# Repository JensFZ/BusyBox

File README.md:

# BusyBox

In diesen Projekt geht es darum, dass man einen Status einer Website abfragt und, je nach rückgabe, eine grüne oder rote LED Schaltet.

der Web API Code wird demnächst auch hier noch hochgeladen

## Einrichtung Arduino IDE

- zusützliche Boardverwalter URL: http://arduino.esp8266.com/stable/package_esp8266com_index.json
- über den Boardverwalter nun das Board "esp8266" suchen und installieren
- Als Board nun über "Werkzeuge" -> "Board" -> "ESP8266 Boards" -> "NodeMCU 1.0 (ESP-12E Module)" auswählen
- Uploadspeed auf 115200 stellen
- Port auf den entsprechenden COM Port stellen

## Verwendete Hardware
- 1x NodeMCU Lua Amica Modul V2 ESP8266 ESP-12F
- 1x LED Green
- 1x LED Red
- 1x DIP-Switch 2 Slide
- 5x 1k Wiederstand
- optional LCD 16x2 i2c

## Contributing
Pull requests sind wilkommen. Bei größeren Änderungen eröffnen Sie bitte zunächst ein Issue, um zu besprechen, was Sie ändern möchten.

## License
[MIT](https://choosealicense.com/licenses/mit/)

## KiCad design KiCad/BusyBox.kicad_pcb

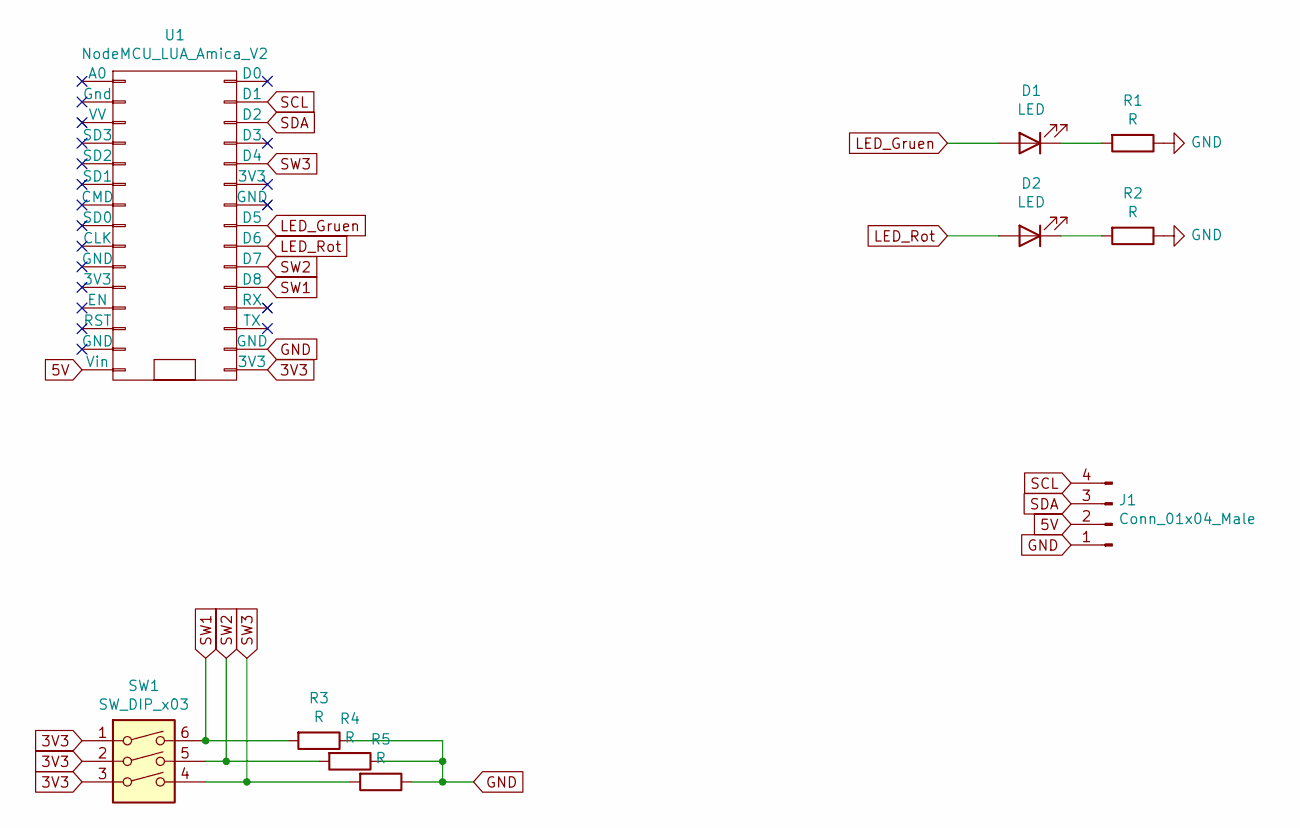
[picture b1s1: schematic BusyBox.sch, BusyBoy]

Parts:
D1, D2: LED; LED_D5.0mm
J1: Conn_01x04_Male; PinHeader_1x04_P2.54mm_Vertical
R1, R2, R3, R4, R5: R; R_Axial_DIN0207_L6.3mm_D2.5mm_P10.16mm_Horizontal
SW1: SW_DIP_x03; SW_DIP_SPSTx03_Slide_9.78x9.8mm_W7.62mm_P2.54mm
U1: NodeMCU_LUA_Amica_V2; NodeMCU-LoLinV3

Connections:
3V3: SW1.1, SW1.2, SW1.3, U1.16 (3V3)
5V: J1.2, U1.15 (Vin)
GND: J1.1, R1.1, R2.1, R3.1, R4.1, R5.1, U1.17 (GND)
LED_Gruen: D1.2 (A), U1.23 (D5)
LED_Rot: D2.2 (A), U1.22 (D6)
unnamed: D1.1 (K), R1.2
unnamed: D2.1 (K), R2.2
SCL: J1.4, U1.29 (D1)
SDA: J1.3, U1.28 (D2)
SW1: R3.2, SW1.6, U1.20 (D8)
SW2: R4.2, SW1.5, U1.21 (D7)
SW3: R5.2, SW1.4, U1.26 (D4)

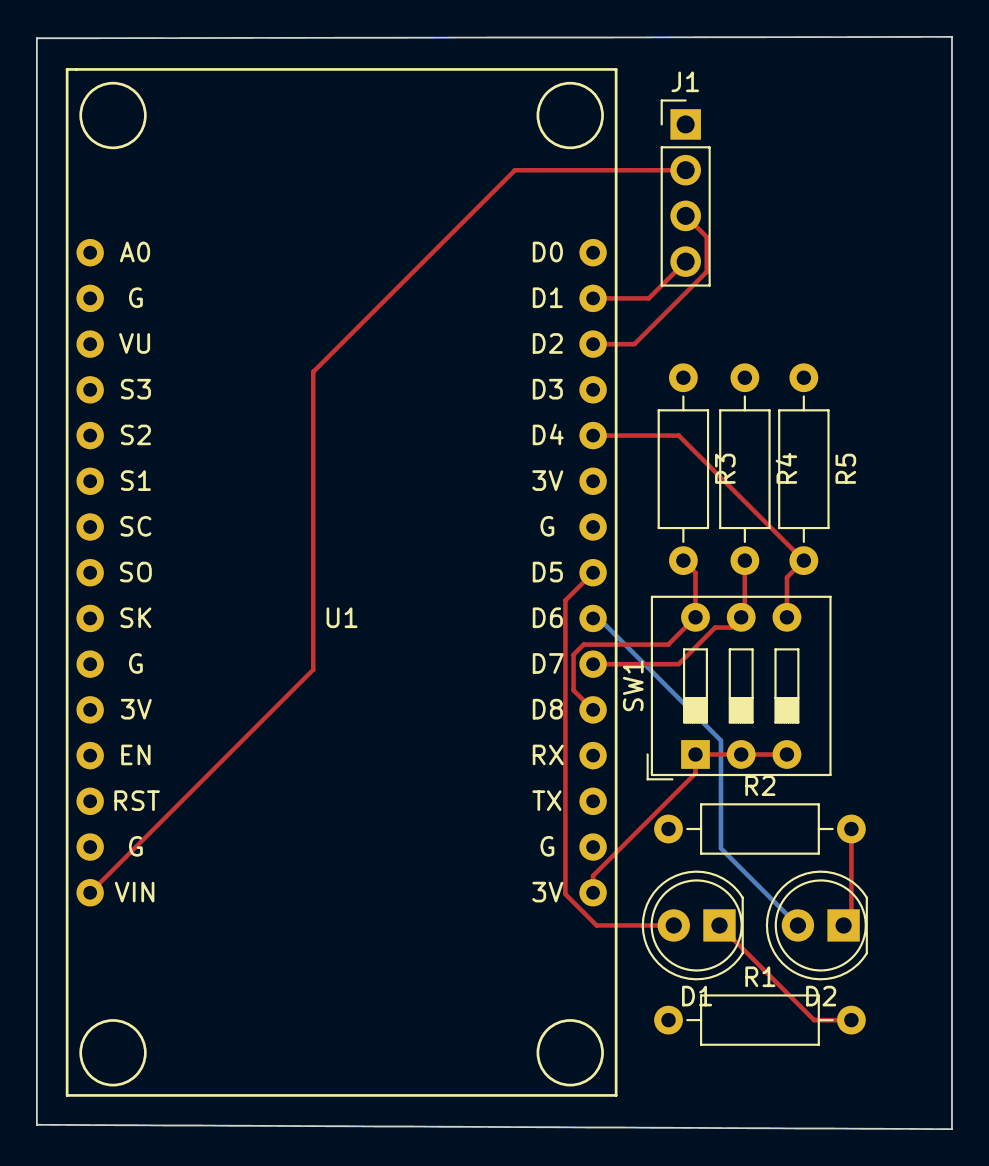
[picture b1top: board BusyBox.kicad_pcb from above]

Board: 2 copper layers, 50.8 x 60.7 mm, 10 parts (0 on the bottom side), 12 nets.

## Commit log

2021-10-14 README angepasst
2021-10-14 README erweitert
2021-10-14 .gitignore hinzugefügt
2021-10-14 Schaltplan erstellt - WIP!
2021-10-19 gitignore angepasst
2021-10-19 Schaltplan und Platine designed
2021-10-19 Code erstellt und angepasst
2021-10-19 BOM erstellt
2021-10-20 switch eingebaut -> noch nicht getestet! API muss true oder Fals für amTelefon geben. somit werden timeouts / Probleme mit der Api nicht als am Telefon interpretiert
2021-10-27 Busybox an BusyBoxNode angepasst
